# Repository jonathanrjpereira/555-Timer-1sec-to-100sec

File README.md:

# 555 Timer 1sec to 100sec
Turn a device ON for a period of 1 to 100 seconds using a 555.

**Full Video:**

**Order PCB:**  [PCBWay](https://bit.ly/2ETyaRc)    

## Electronic Components
| Qty | Component | Buy |
| ------------- | ------------- | ------------- |
| 1 | 555 |[AliExpress](http://s.click.aliexpress.com/e/sCv1ACC) |
| 2 | 3KΩ Resistor |[AliExpress](http://s.click.aliexpress.com/e/bh4eqrQs) |
| 4 | 10KΩ Resistor |[AliExpress](http://s.click.aliexpress.com/e/bh4eqrQs) |
| 1 | 1MΩ Potentiometer |[AliExpress](http://s.click.aliexpress.com/e/bR23nRuG) |
| 1 | IN4004 Diode |[AliExpress](http://s.click.aliexpress.com/e/HW1fm16) |
| 2 | Tactile Momentary Push Buttons |[AliExpress](http://s.click.aliexpress.com/e/c77Ajrpq) |
| 2 | 5mm LED |[AliExpress](http://s.click.aliexpress.com/e/wuFpLXS) |
| 2 | 100uF Capacitor |[AliExpress](http://s.click.aliexpress.com/e/c9FHzl5W) |
| 2 | 0.1uF (100nF) Capacitor |[AliExpress](http://s.click.aliexpress.com/e/byQG0DZW) |
| 1 | 2 Pin Screw Terminal |[AliExpress](http://s.click.aliexpress.com/e/bj5UNUs0) |
| 1 | 3 Pin Screw Terminal |[AliExpress](http://s.click.aliexpress.com/e/bj5UNUs0) |
| 1 | 12VDC Relay |[AliExpress](http://s.click.aliexpress.com/e/xyrHlu8) |
| 1 | 12VDC Adapter |[AliExpress](http://s.click.aliexpress.com/e/V0x0bms) |
| 1 | SPDT Slide Switch |[AliExpress](http://s.click.aliexpress.com/e/cDjWUvjK) |
| 1 | PCB |[AliExpress](http://s.click.aliexpress.com/e/dhgwzKY) |

| Tools | Buy |
|--|--|
|Soldering Iron|[AliExpress](http://s.click.aliexpress.com/e/E83bSJI) |
|Soldering Wire|[AliExpress](http://s.click.aliexpress.com/e/PdhB0nm) |
|Mini PCB Hand Drill + Bits|[AliExpress](http://s.click.aliexpress.com/e/b93tomjI) |
|Wire Cutter|[AliExpress](http://s.click.aliexpress.com/e/bHFL9vLi) |
|Wire Stripper|[AliExpress](http://s.click.aliexpress.com/e/4yJWedw) |
|Soldering Helping Hands|[AliExpress](http://s.click.aliexpress.com/e/cAQ2StNm) |

## Working
**LM555/NE555:**

The 555 is a highly stable device for generating accurate time delays or oscillation. Additional terminals are provided for triggering or resetting if desired. In the time delay mode of operation, the time is precisely controlled by one external resistor and capacitor. The circuit may be triggered and reset on falling waveforms, and the output circuit can source or sink up to 200mA or drive TTL circuits.

**Circuit:**

In the Monostable mode, the LM555 timer acts as a one shot pulse generator. The pulses being when the LM555 timer receives a signal at the trigger input that falls below a 1/3 of the voltage supply. The width of the output pulse is determined by the time constant of an RC network. The output pulse ends when the voltage on the capacitor equals 2/3 of the supply voltage. The output pulse width can be extended or shortened depending on the application by adjusting the R and C values.

The external capacitor is initially discharged by a transistor inside the timer. Upon application of a negative trigger pulse of less than 1/3 VCC to pin 2, the internal flip-flop is set which both releases the short circuit across the capacitor and drives the output high.

The voltage across the capacitor then increases exponentially for a period of t = 1.1RC , at the end of which the voltage equals 2/3 VCC. The internal comparator then resets the flip-flop which in turn discharges the capacitor and drives the output to its low state.

The figure above shows the waveforms generated in this mode of operation. Since the charge and the threshold level of the comparator are both directly proportional to supply voltage, the timing interval is independent of supply.

Separate input triggers are used to start and reset the timer. The RC network determines the period of the output pulse. High power appliances can be controlled through a relay acting as a switch.

The LM555 has a maximum typical supply voltage rating of 16V while the relay's armature coil is enabled at 12V. Hence a 12V power supply is used to minimize the number of components such as linear voltage regulators. When pin 2 of the LM555 is triggered (by shorting it to ground) through the momentary switch S1, the timer is started.

The timer generates an output pulse with an ON time period determined by the RC network i.e t = 1.1RC . In this case, the fixed value of the capacitor is 100uF. The value of R consists of a 10KΩ resistor in series with a 1MΩ potentiometer. We can vary the potentiometer to change the time period of the output pulse.

For example, if the potentiometer is set to 0Ω, the value of R is equal to 10KΩ.
Hence t = 1.1 x 10K x 100u = 1 second.

But if the pot is set to 1MΩ, the value of R is equal to 1MΩ + 10KΩ = 1010KΩ.
Hence t = 1.1 x 1010K x 100u = 100 seconds.

When pin 4 of the LM555 is triggered (by shorting it to ground) through the momentary switch S2, the timer is reset.

When the timer starts, the relay turns ON. Hence the Common(COM) terminal of the relay is shorted to the Normally Open (NO) terminal. A high power load can be connected to this terminal such as a light bulb or water pump. A transistor Q1 acts as a switch an ensures sufficient drive current is provided to the relay. Diode D1 acts as a flyback diode which protects the transistor Q1 from voltage spikes caused by the relay coil.

LED2 turns on in order to indicate when the relay is turned ON. LED1 indicates the circuit is powered ON. An SPDT switch S3 is used to switch the circuit ON. Capacitors C2 and C4 are used to filter noise in the supply line.

## Contributing🛠
Are you an engineer or hobbyist who has a great idea for a new feature in this project? Maybe you have a good idea for a bug fix? Feel free to grab our code & schematics from Github and tinker with it. Don't forget to smash ⭐️ & the Pull Request button.

[![alt text][1.1]][1] [![alt text][2.1]][2] [![alt text][3.1]][3]

[1.1]: https://github.com/jonathanrjpereira/Social-Media-README/blob/master/youtube.png (YouTube)
[2.1]: https://github.com/jonathanrjpereira/Social-Media-README/blob/master/instagram.png (Instagram)
[3.1]: https://github.com/jonathanrjpereira/Social-Media-README/blob/master/github.png (GitHub)

[1]: https://www.youtube.com/channel/UCRW-41O1vy98KKgJRQoYzdg
[2]: https://www.instagram.com/electroguruji/
[3]: https://github.com/jonathanrjpereira

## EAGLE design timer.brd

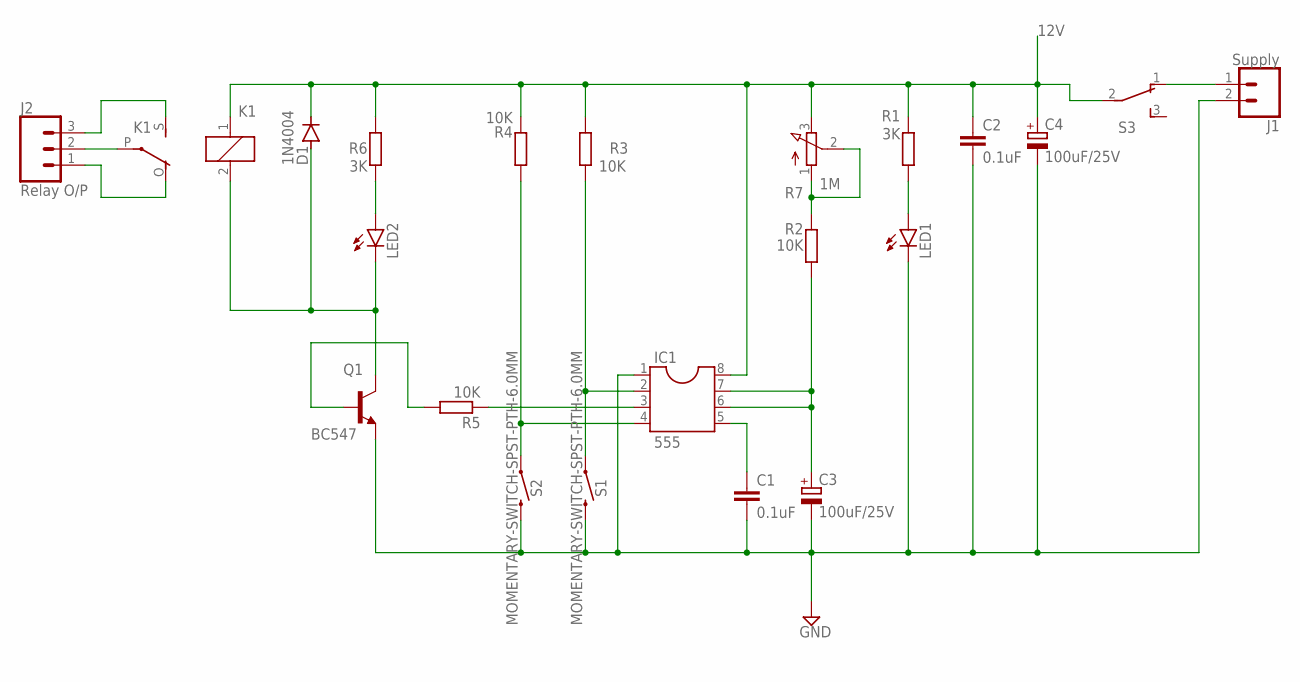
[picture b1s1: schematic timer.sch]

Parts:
C1, C2: 0.1uF; C025-050X050
C3, C4: 100uF/25V; E2,5-6
D1: 1N4004; DO41-10
IC1: 555; SOCKET-08
J1: Supply; SCREWTERMINAL-5MM-2
J2: Relay O/P; SCREWTERMINAL-5MM-3
K1: ZF112
LED1, LED2: LED5MM
Q1: BC547; TO92
R1, R6: 3K; 0207/10
R2, R3, R4, R5: 10K; 0207/10
R7: 1M; 3RP/1610N
S1, S2: MOMENTARY-SWITCH-SPST-PTH-6.0MM; TACTILE_SWITCH_PTH_6.0MM
S3: TL36YO; TL3XYO

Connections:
12V: C2.1, C4.+, D1.C, IC1.8, K1.1, R1.2, R3.2, R4.2, R6.2, R7.3 (E), S3.2
GND: C1.2, C2.2, C3.-, C4.-, IC1.1, J1.2, LED1.K (C), Q1.1 (E), S1.3 (2), S2.3 (2)
unnamed: C3.+, IC1.6, IC1.7, R2.1
unnamed: R2.2, R7.1 (A), R7.2 (S)
unnamed: C1.1, IC1.5
unnamed: IC1.4, R4.1, S2.1
unnamed: IC1.2, R3.1, S1.1
unnamed: IC1.3, R5.1
unnamed: Q1.2 (B), R5.2
unnamed: D1.A, K1.2, LED2.K (C), Q1.3 (C)
unnamed: J2.2, K1.P
unnamed: LED2.A, R6.1
unnamed: J1.1, S3.1 (O)
unnamed: J2.3, K1.S
unnamed: J2.1, K1.O
unnamed: LED1.A, R1.1

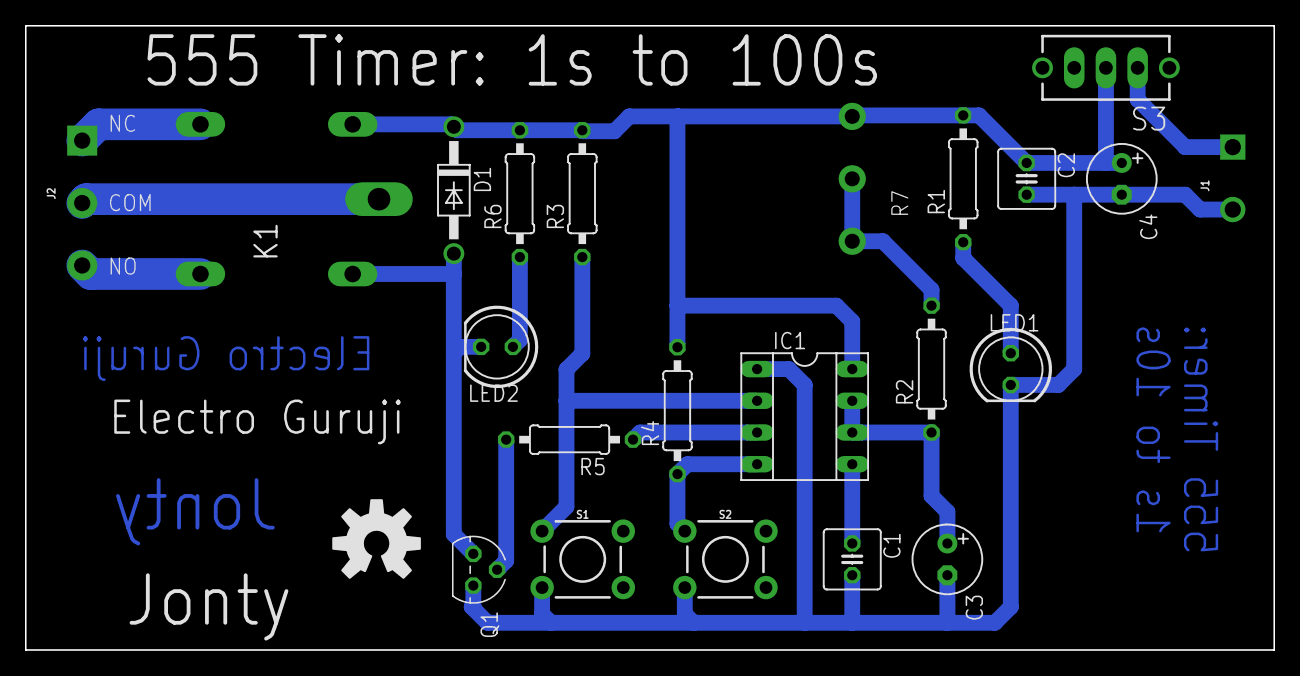
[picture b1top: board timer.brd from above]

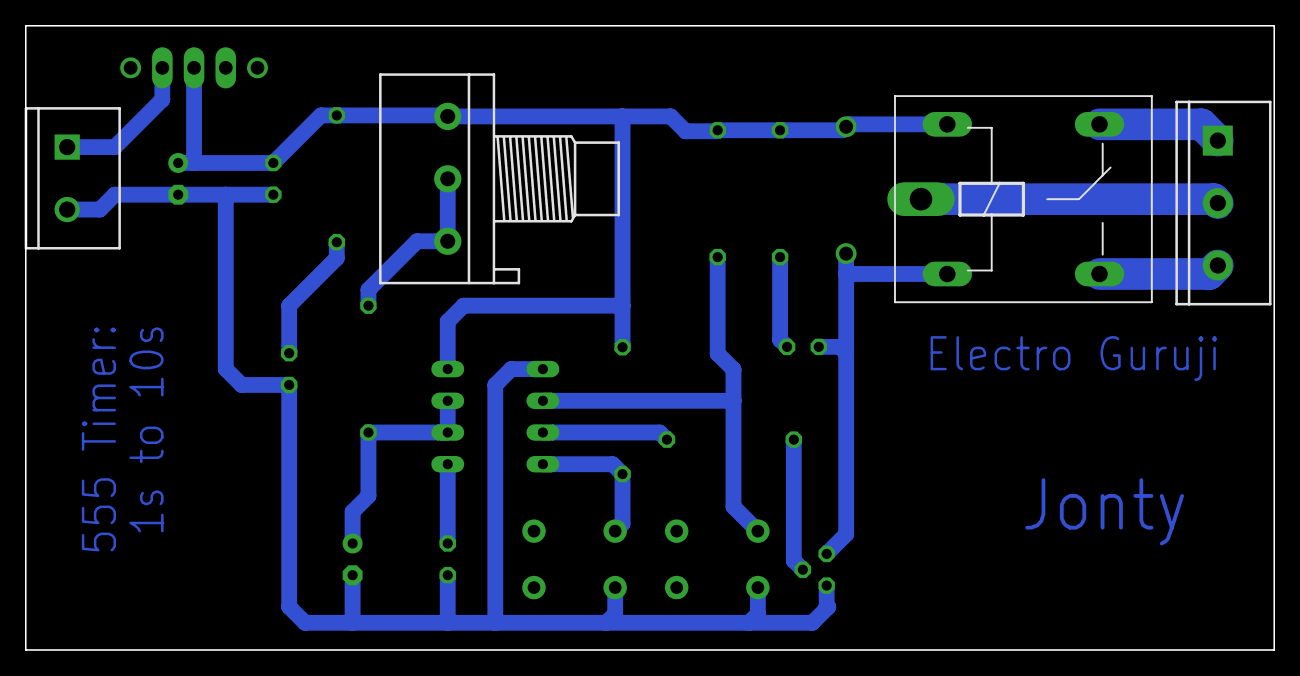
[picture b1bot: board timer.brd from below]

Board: 2 copper layers, 100.0 x 50.0 mm, 23 parts (4 on the bottom side), 16 nets.

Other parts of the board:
U$1: OSHW-LOGO-L

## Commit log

2019-03-14 Schematic
2019-03-14 Board
2019-03-14 Working
2019-03-14 Single Side PCB printable
2019-03-14 Electronic Components
2019-03-23 12V Relay
2019-05-30 Images
2019-06-04 BOM, Gerber, Video

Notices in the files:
parts and their libraries:
SparkFun-Switches: Licensing: Creative Commons ShareAlike 4.0 International - https://creativecommons.org/licenses/by-sa/4.0
